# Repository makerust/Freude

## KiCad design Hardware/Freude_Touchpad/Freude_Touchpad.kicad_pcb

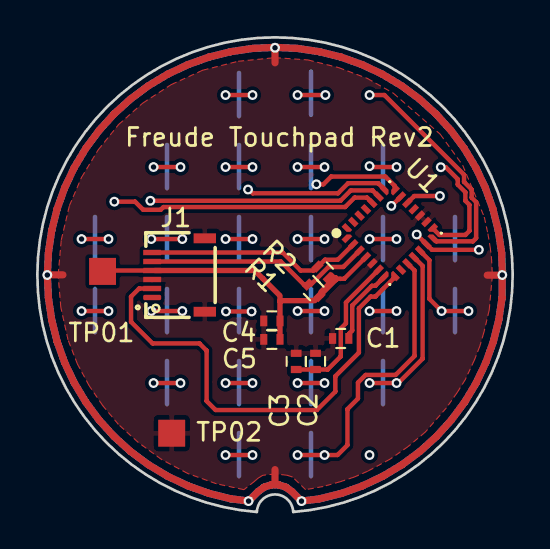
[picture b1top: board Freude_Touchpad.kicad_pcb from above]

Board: 2 copper layers, 26.4 x 26.4 mm, 11 parts (0 on the bottom side), 7 nets.

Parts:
C1: C_Small; R_0402
C2, C4: 100pF; R_0402
C3, C5: 1uF; R_0402
J1: Conn_01x06_Female; 503480-0600
R1, R2: 4.7k; R_0402
TP01, TP02: Measurement_Point_Square-SMD-Pad_Small
U1: IQS572

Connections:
+3.3VA: C4.2, C5.2, J1.4, R1.1, R2.1, TP01.1, U1.4
/NRST: C1.1, U1.7
/RDY_TP: J1.2, U1.8
/SCL_TP: J1.5, R1.2, U1.3
/SDA_TP: J1.6, R2.2, U1.2
GNDA: C1.2, C2.1, C3.1, C4.1, C5.1, J1.0, J1.3, TP02.1, U1.5, U1.16, U1.17
unnamed: C2.2, C3.2, U1.6

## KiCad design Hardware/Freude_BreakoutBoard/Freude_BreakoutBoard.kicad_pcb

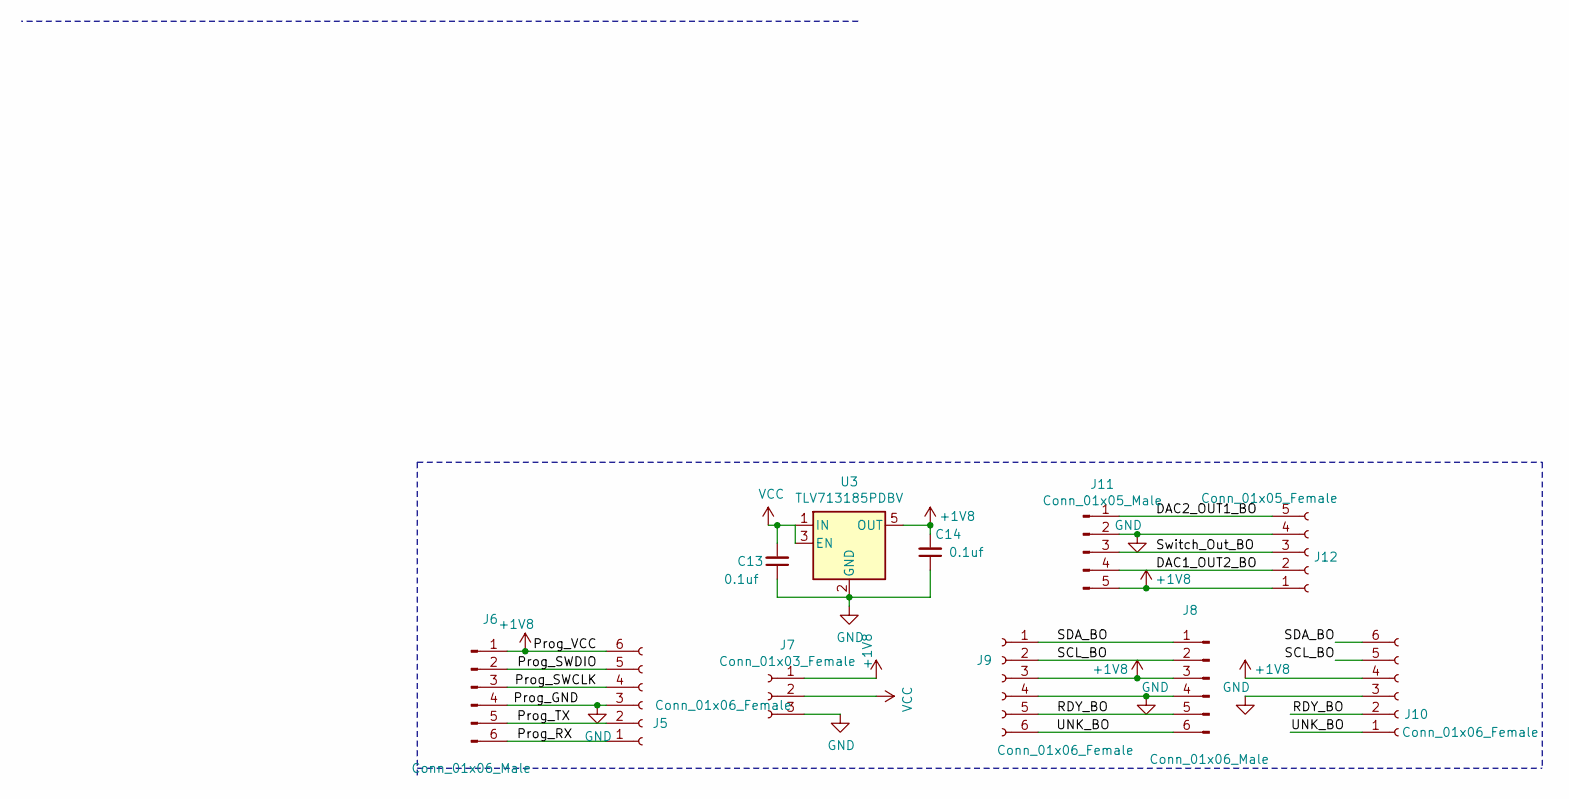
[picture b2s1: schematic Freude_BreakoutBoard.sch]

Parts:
C13, C14: 0.1uf; R_0603
J5, J9, J10: Conn_01x06_Female; 503480-0600
J6, J8: Conn_01x06_Male; 1X06-KIT
J7: Conn_01x03_Female; 1X03
J11: Conn_01x05_Male; 1X05
J12: Conn_01x05_Female; 503480-0500
U3: TLV713185PDBV; SOT-23-5

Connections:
+1V8: C14.2, J5.6, J6.1, J7.1, J8.3, J9.3, J10.4, J11.5, J12.1, U3.5 (OUT)
/DAC1_OUT2_BO: J11.4, J12.2
/DAC2_OUT1_BO: J11.1, J12.5
/Prog_RX: J5.1, J6.6
/Prog_SWCLK: J5.4, J6.3
/Prog_SWDIO: J5.5, J6.2
/Prog_TX: J5.2, J6.5
/RDY_BO: J8.5, J9.5, J10.2
/SCL_BO: J8.2, J9.2, J10.5
/SDA_BO: J8.1, J9.1, J10.6
/Switch_Out_BO: J11.3, J12.3
/UNK_BO: J8.6, J9.6, J10.1
GND: C13.1, C14.1, J5.3, J6.4, J7.3, J8.4, J9.4, J10.3, J11.2, J12.4, U3.2 (GND)
VCC: C13.2, J7.2, U3.1 (IN), U3.3 (EN)

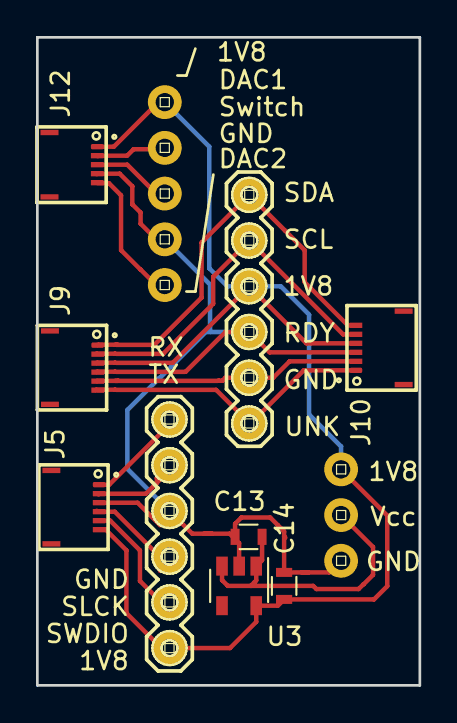
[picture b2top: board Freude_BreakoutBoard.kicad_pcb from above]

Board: 2 copper layers, 21.2 x 36.0 mm, 11 parts (0 on the bottom side), 14 nets.

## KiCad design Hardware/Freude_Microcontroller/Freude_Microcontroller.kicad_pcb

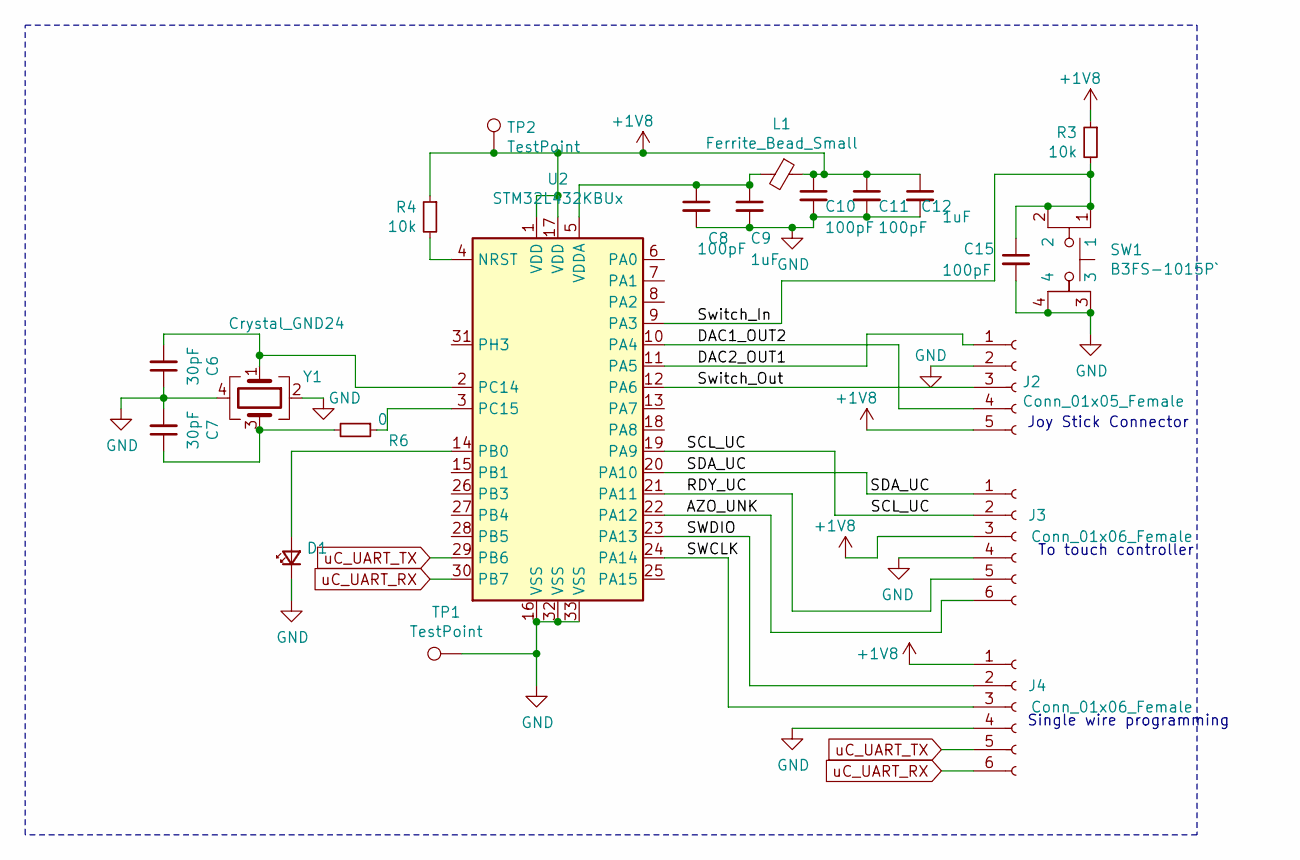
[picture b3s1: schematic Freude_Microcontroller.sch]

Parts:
C6, C7: 30pF; R_0402
C8, C10, C11, C15: 100pF; R_0402
C9, C12: 1uF; R_0402
D1: 16-213/GHC-YR1S1/3T; LED_0402
J2: Conn_01x05_Female; 503480-0500
J3, J4: Conn_01x06_Female; 503480-0600
L1: Ferrite_Bead_Small; R_0402
R3, R4: 10k; R_0402
R6: 0; R_0402
SW1: B3FS-1015P`; B3FS-1015P
TP1, TP2: TestPoint; Measurement_Point_Square-SMD-Pad_Small
U2: STM32L432KBUx; QFN-32-1EP_5x5mm_P0.5mm_EP3.45x3.45mm
Y1: Crystal_GND24; Crystal_SMD_5032-4pin_5.0x3.2mm; MFG Partnumber ABM3B-8.000MHZ-B2-T

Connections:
+1V8: C10.1, C11.1, C12.1, J2.5, J3.3, J4.1, L1.1, R3.1, R4.1, TP2.1, U2.1 (VDD), U2.17 (VDD)
/AZO_UNK: J3.6, U2.22 (PA12)
/DAC1_OUT2: J2.4, U2.10 (PA4)
/DAC2_OUT1: J2.1, U2.11 (PA5)
/RDY_UC: J3.5, U2.21 (PA11)
/SCL_UC: J3.2, U2.19 (PA9)
/SDA_UC: J3.1, U2.20 (PA10)
/SWCLK: J4.3, U2.24 (PA14)
/SWDIO: J4.2, U2.23 (PA13)
/Switch_In: C15.1, R3.2, SW1.1, SW1.2, U2.9 (PA3)
/Switch_Out: J2.3, U2.12 (PA6)
GND: C6.1, C7.2, C8.2, C9.2, C10.2, C11.2, C12.2, C15.2, D1.1 (K), J2.2, J3.4, J4.4, SW1.3, SW1.4, TP1.1, U2.16 (VSS), U2.32 (VSS), U2.33 (VSS), Y1.2, Y1.4
unnamed: C6.2, U2.2 (PC14), Y1.1
unnamed: C7.1, R6.2, Y1.3
unnamed: C8.1, C9.1, L1.2, U2.5 (VDDA)
unnamed: D1.2 (A), U2.14 (PB0)
unnamed: R4.2, U2.4 (NRST)
unnamed: R6.1, U2.3 (PC15)
uC_UART_RX: J4.6, U2.30 (PB7)
uC_UART_TX: J4.5, U2.29 (PB6)

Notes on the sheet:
Joy Stick Connector
To touch controller
Single wire programming

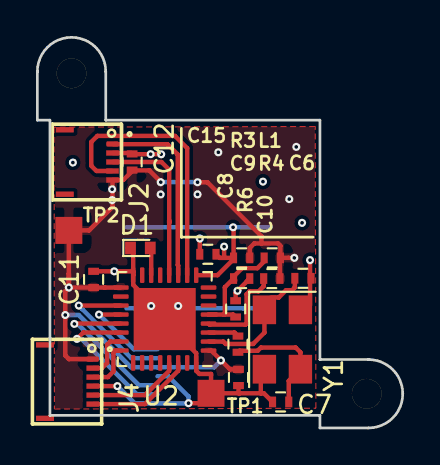
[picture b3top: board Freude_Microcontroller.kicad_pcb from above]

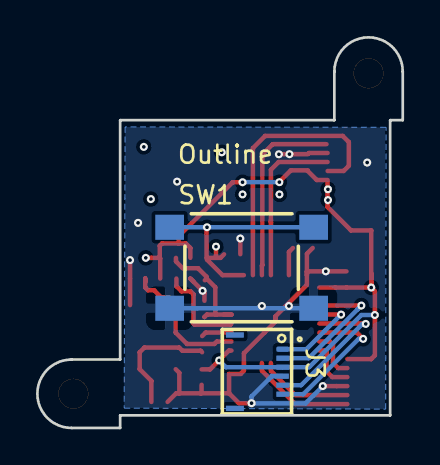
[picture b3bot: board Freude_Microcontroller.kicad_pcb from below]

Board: 4 copper layers, 20.3 x 21.7 mm, 22 parts (3 on the bottom side), 20 nets.

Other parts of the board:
Outline: Joystick Envelope

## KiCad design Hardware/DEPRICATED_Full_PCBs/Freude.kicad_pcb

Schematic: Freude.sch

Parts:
C1: C_Small; R_0402
C2, C4, C8, C10, C11, C15: 100pF; R_0402
C3, C5, C9, C12: 1uF; R_0402
C6, C7: 30pF; R_0402
C13, C14: 0.1uf; R_0603
D1: 16-213/GHC-YR1S1/3T; LED_0402
J1, J3, J4, J5, J9, J10: Conn_01x06_Female; 503480-0600
J2, J12: Conn_01x05_Female; 503480-0500
J6, J8: Conn_01x06_Male; 1X06-KIT
J7: Conn_01x03_Female; 1X03
J11: Conn_01x05_Male; 1X05
L1: Ferrite_Bead_Small; R_0402
R1, R2: 4.7k; R_0402
R3, R4: 10k; R_0402
R6: 0; R_0402
SW1: B3FS-1015P`; B3FS-1015P
TP1, TP2: TestPoint; Measurement_Point_Square-SMD-Pad_Small
U1: IQS572
U2: STM32L432KBUx; QFN-32-1EP_5x5mm_P0.5mm_EP3.45x3.45mm
U3: TLV713185PDBV; SOT-23-5
X1: Custom_Touchpad; Touchpad
Y1: Crystal_GND24; Crystal_SMD_5032-4pin_5.0x3.2mm; MFG Partnumber ABM3B-8.000MHZ-B2-T

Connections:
+1V8: C4.2, C5.2, C10.1, C11.1, C12.1, C14.2, J1.3, J2.5, J3.3, J4.1, J5.1, J6.1, J7.1, J8.3, J9.3, J10.3, J11.5, J12.5, L1.1, R1.1, R2.1, R3.1, R4.1, TP2.1, U1.4, U2.1, U2.17, U3.5 (OUT)
/AZO_UNK: J3.6, U2.22
/DAC1_OUT2: J2.4, U2.10
/DAC1_OUT2_BO: J11.4, J12.4
/DAC2_OUT1: J2.1, U2.11
/DAC2_OUT1_BO: J11.1, J12.1
/PGM: U1.27
/Prog_RX: J5.6, J6.6
/Prog_SWCLK: J5.3, J6.3
/Prog_SWDIO: J5.2, J6.2
/Prog_TX: J5.5, J6.5
/RDY_BO: J8.4, J9.4, J10.4
/RDY_TP: J1.5, U1.8
/RDY_UC: J3.5, U2.21
/SCL_BO: J8.2, J9.2, J10.2
/SCL_TP: J1.2, R1.2, U1.3
/SCL_UC: J3.2, U2.19
/SDA_BO: J8.1, J9.1, J10.1
/SDA_TP: J1.1, R2.2, U1.2
/SDA_UC: J3.1, U2.20
/SWCLK: J4.3, U2.24
/SWDIO: J4.2, U2.23
/SW_IN: U1.28
/Switch_In: C15.1, R3.2, SW1.1, SW1.2, U2.9
/Switch_Out: J2.3, U2.12
/Switch_Out_BO: J11.3, J12.3
/UNK_BO: J8.6, J9.6, J10.6
GND: C1.2, C2.1, C3.1, C4.1, C5.1, C6.1, C7.2, C8.2, C9.2, C10.2, C11.2, C12.2, C13.1, C14.1, C15.2, D1.1, J1.4, J2.2, J3.4, J4.4, J5.4, J6.4, J7.3, J8.5, J9.5, J10.5, J11.2, J12.2, SW1.3, SW1.4, TP1.1, U1.5, U2.16, U2.32, U2.33, U3.2 (GND), Y1.2, Y1.4
unnamed: C2.2, C3.2, U1.6
unnamed: C6.2, U2.2, Y1.1
unnamed: C7.1, R6.2, Y1.3
unnamed: C8.1, C9.1, L1.2, U2.5
unnamed: D1.2, U2.14
unnamed: R4.2, U2.4
unnamed: R6.1, U2.3
VCC: C13.2, J7.2, U3.1 (IN), U3.3 (EN)
XA00: U1.18, X1.XA00
XA01: U1.19, X1.XA01
XA02: U1.20, X1.XA02
XA03: U1.21, X1.XA03
XA04: U1.22, X1.XA04
XA05: U1.23, X1.XA05
XA06: U1.24, X1.XA06
YA00: U1.10, X1.YA00
YA01: U1.11, X1.YA01
YA02: U1.12, X1.YA02
YA03: U1.13, X1.YA03
YA04: U1.14, X1.YA04
YA05: U1.15, X1.YA05
uC_UART_RX: J4.6, U2.30
uC_UART_TX: J4.5, U2.29

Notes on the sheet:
Joy Stick Connector
To touch controller
Single wire programming

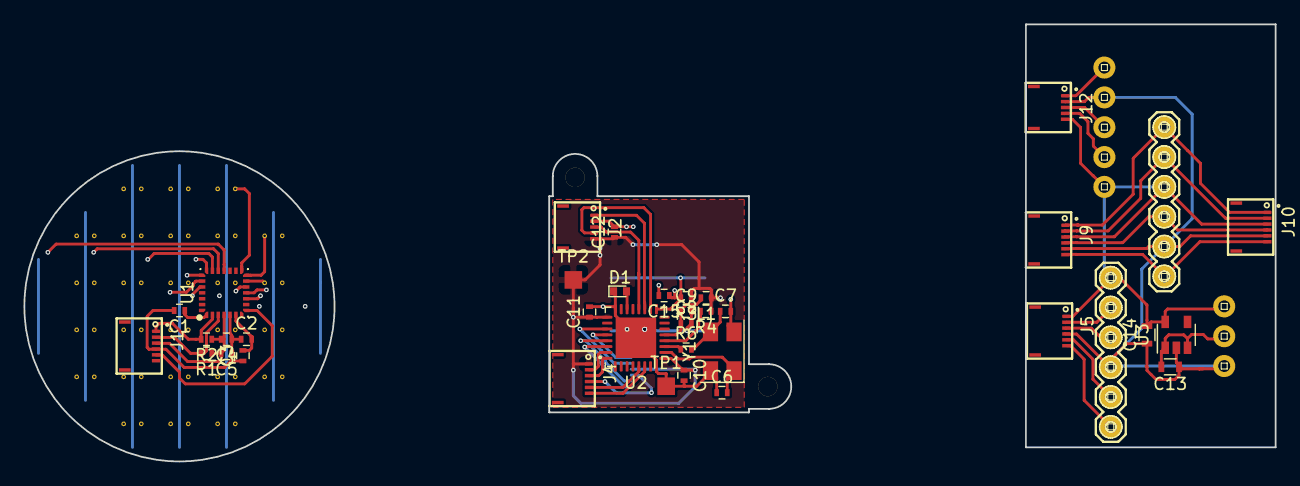
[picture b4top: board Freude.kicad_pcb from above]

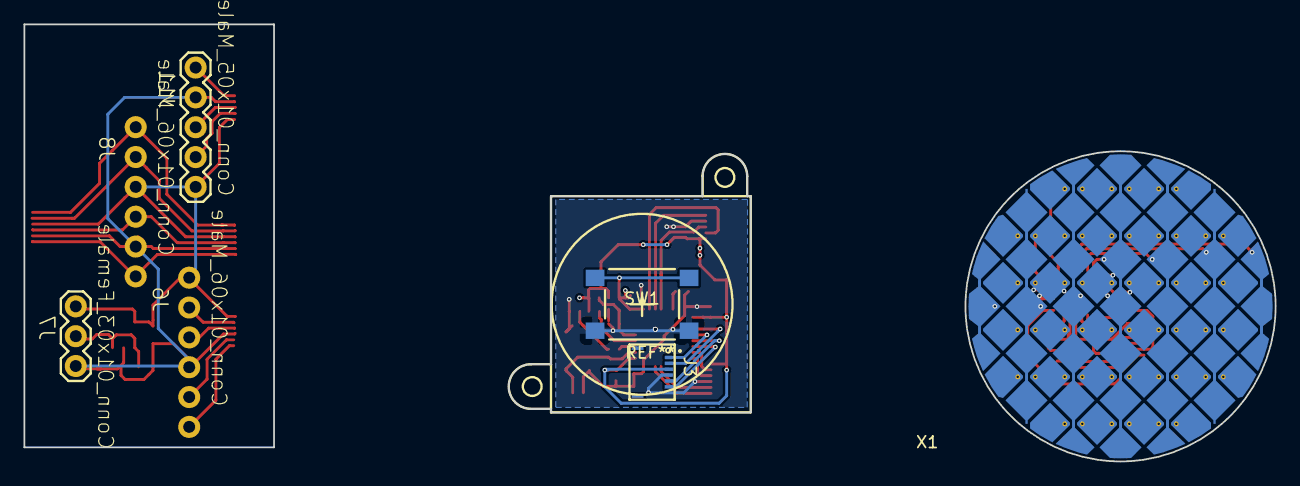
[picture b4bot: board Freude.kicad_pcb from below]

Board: 4 copper layers, 106.5 x 37.2 mm, 42 parts (3 on the bottom side), 49 nets.

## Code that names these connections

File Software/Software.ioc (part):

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Mcu.Name=STM32L432K(B-C)Ux
Mcu.Package=UFQFPN32
Mcu.UserName=STM32L432KBUx
PA10.Mode=I2C
PA10.Signal=I2C1_SDA
PA11.Signal=GPXTI11
PA13\ (JTMS-SWDIO).Mode=Serial_Wire
PA13\ (JTMS-SWDIO).Signal=SYS_JTMS-SWDIO
PA14\ (JTCK-SWCLK).Mode=Serial_Wire
PA14\ (JTCK-SWCLK).Signal=SYS_JTCK-SWCLK
PA3.Signal=GPXTI3
PA4.Signal=COMP_DAC11_group
PA5.Signal=COMP_DAC12_group
PA6.Signal=GPIO_Output
PA9.Mode=I2C
PA9.Signal=I2C1_SCL
PB0.Signal=GPIO_Output
PB6.Mode=Asynchronous
PB6.Signal=USART1_TX
PB7.Mode=Asynchronous
PB7.Signal=USART1_RX
PC14-OSC32_IN\ (PC14).Signal=GPIO_Analog
PC15-OSC32_OUT\ (PC15).Signal=GPIO_Analog
PH3-BOOT0.GPIOParameters=PinState,GPIO_PuPd,GPIO_Label
PH3-BOOT0.GPIO_Label=TestName
PH3-BOOT0.GPIO_PuPd=GPIO_NOPULL
PH3-BOOT0.PinState=GPIO_PIN_RESET
PH3-BOOT0.Signal=GPIO_Output
RCC.HSE_VALUE=8000000
board=custom

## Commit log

2020-05-23 inital commit
2020-05-25 Added readme
2020-05-27 added a 7x8 diamond touch sensor as a sketch
2020-05-27 remove error README.md.txt
2020-06-11 azoteq IQS562 as new touch controller
2020-06-11 adding net
2020-06-11 Add Hardware dir, move HW files
2020-06-28 Add software folder w/ cpp w/ rxtx lane read write
2020-06-29 add functions ReadTouchStrength ReadTouchAre ReadXAbs ReadYAbs
2020-07-20 Add cube mx files for the chosen uc
2020-07-20 Add uc, inter connects, futter to schematic
2020-07-21 add jtag lines
2020-07-21 add UART
2020-07-22 change debug header to 9 pin for uart, add 5 pin connector to con
2020-07-22 added 5 pin connector, added envelope for uc board, changed uc to low power smaller footprint after seeing envelope
2020-07-22 change uc for smaller footprint, lower input voltage.
2020-07-23 add connectors, symbol for touch pad, start placement of touch controller
2020-07-25 Route touchpad complete *airhorn*, add switch schematic, add domain boxes schematic
2020-07-25 fix several power connection errors on U2 -power and ground, perhaps- added 6-pin connector to touch pad to match brain board after rejecting 180 deg connector
2020-07-26 add detail to joystick envelope, changed sides of connectors to better fit joystick, reroute in progress
2020-07-26 add custom 3d part for IQS572
2020-07-26 create part B3FS-1015p include 3d file. Add to PCB
2020-07-26 define boards edges
2020-07-27 added connectors for debug board.
2020-07-28 add led, change sw1 footprint, add testpads
2020-07-28 rearrange and rerout
2020-07-29 rerouted, tidied
2020-07-29 routing on boards finished. Will change to 3 board projects for 3d reasons. Considering branch
2020-07-29 finished routing. consider branch, will split project into 3 boards to make 3d assy possible
2020-08-05 Creat one project director just for the touchpad PCB, remade the touchpad part as pours to avoid via shorts
2020-08-08 broke PCB file into 3 folders and 3 PCB projects for each of the PCBAs, to make 3D drafting simpler. Created 3D housing project.
2020-08-08 remove depricated file
2020-08-08 remove further depricated files
2020-08-11 Bottom housing near finish. Mating pockets added, cut out for conn refined, critical edges chamfered or fileted.
2020-08-15 made outline smaller to fit housing, subsequent rerouting
2020-08-16 add stem and flange to top housing
2020-08-18 Changed location of connector to make routing of cable easier
2020-08-18 Finished top housing, added cap part, release candidate
2020-08-30 add photos of prototype housings fitment
2020-08-30 add prototype release output files
2020-08-30 remove inner layers
2020-08-30 silk layout, proto release candidate
2020-08-30 prototype cadidate
2020-09-01 change hole size to 0.45mm, decrease soldermask expansion
2020-09-03 add silk to breakout :|
2020-09-07 Closes #1, replaces compliant retention mechanism with pin
2020-09-07 resolves #2, resolves #3
2020-09-20 Debug branch first commit
2020-09-24 revised functions, does not build but it's late
2020-09-27 added first steps functionality.
2020-09-27 lots of changes from Alex Shirley, I2C not finished but better
2020-10-03 untested schedulerer
2020-10-29 initial branch commit, purpose dev on Nucleo dev board
2020-11-03 rite exact channels
2020-11-18 added ground pour and ground ring
2020-11-27 resolves 10, resolves 9, resolves 6, resolves 5, add ground ring around touch sensor, add ground ring on top, separate RX from TX and include ground plane between
2020-11-27 resolves #10, resolves #9, resolves #6, resolves #5, add ground ring around touch sensor, add ground ring on top, separate RX from TX and include ground plane between
